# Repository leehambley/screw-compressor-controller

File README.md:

# Screw compressor controller

A replacement controller for a Ceccato ES3000-based 3-phase screw compressor
whose original control board died (blown triac, damaged optocouplers and
traces). It holds a pressure setpoint by running the motor's variable-frequency
drive at the right speed, watches the temperatures, and has a touch screen for
the operator.

*The operator screen (480×480). Rendered from the real UI source with the same
renderer and fonts the board uses; see [Previewing the UI](#previewing-the-ui).*

## The machine

| | |
|---|---|
| Compressor | Ceccato ES3000 screw compressor, rated 10 bar, run at 8 bar |
| Motor | WEG W22 Premium, 7.5 kW, 400 V, 2-pole, 50 Hz |
| Drive | SAKO SKI-70 VFD, controlled entirely over Modbus RTU (no analog speed signal) |
| Sensors | 2 × 4–20 mA pressure transmitters (0–17 bar), up to 3 × 100k NTC probes |
| Valves | start-assist (blow-down to intake) and condensate drain, both 24 V solenoids |

There is no load/unload air valve. Capacity is controlled by VFD speed alone:
a PID loop holds the setpoint pressure. The start-assist valve only works
during the start-up ramp, and the drain is manual or timed.

## Hardware

Two boards, stacked and screwed together, in one enclosure:

1. **Waveshare ESP32-S3-Touch-LCD-4, Rev 4.0**: the brain and the display.
   ESP32-S3-WROOM-1-N16R8 (16 MB flash, 8 MB PSRAM), 4″ 480×480 panel
   (ST7701S, RGB interface), GT911 capacitive touch, a CH32V003 helper chip
   (panel and touch resets, backlight), and an onboard RS485 transceiver.
2. **The [piggyback](Piggyback/)**: a 100 × 80 mm SMD board, assembled by
   JLCPCB, that does everything the Waveshare can't. It connects to the
   Waveshare through its 10-pin H4 header only (power, I²C and the RS485 pair),
   because every ESP32-S3 pin is already used by the display.

```mermaid
flowchart LR
    PSU["24 V DC supply"] --> PB
    subgraph Module["Display module (one stack)"]
        WS["Waveshare ESP32-S3-Touch-LCD-4<br/>touch UI, control loop"]
        PB["Piggyback I/O board"]
        WS <-->|"H4: 24 V, I²C, RS485"| PB
    end
    PB -->|"RS485 A/B (Modbus)"| VFD["SAKO SKI-70 VFD"]
    PB -->|"enable opto (X1)"| VFD
    P["2 × 4–20 mA pressure"] --> PB
    T["3 × NTC probes"] --> PB
    PB -->|"MOSFET + PWM hold"| V["start-assist and drain valves"]
```

### The piggyback

| Block | Parts |
|---|---|
| Analog inputs | 2 × ADS1115 (16-bit, I²C): two 4–20 mA loops through 100 Ω shunts, three NTC dividers |
| Valve drive | PCA9685 PWM chip, low-side MOSFETs, flyback diodes (full drive to pull in, then a PWM hold) |
| Over-temperature cutout | LM393 comparators on the rotor and motor NTCs, independent of the firmware |
| Watchdog | 74LVC1G123 monostable: the firmware must toggle a heartbeat line about 5 times a second |
| Safety gating | 74LVC08: valves and the VFD enable output only work while the watchdog **and** the temperature cutout are OK |
| VFD enable | optocoupler on the drive's X1 input, set to coast-stop when open |

If the S3 hangs, the piggyback loses power, or a probe reads too hot, the
valves drop out and the VFD's enable input opens, which is set up to coast the
motor to a stop, with no software involved (the drive setting is still to be
verified on the real drive). The
full design, pin allocation and mounting are in
[Piggyback/README.md](Piggyback/README.md) and
[Piggyback/pin-allocation.md](Piggyback/pin-allocation.md).

The piggyback screws to the back of the Waveshare on four 20 mm M2.5 standoffs:

```
 front ->  [ cover glass 84.2 x 84.2 ]
           [ Waveshare PCB 74.5 x 76.5 ]   H4 plug sticks out of its back face
                ||  4x M2.5 standoffs, 20 mm
           [ piggyback 100 x 80, parts facing away from the display ]
```

### Wiring

Only the pressure transmitter colours are fixed (brown = +24 V, green = signal). Every other colour marked "suggested" is a convention for this harness. Pick your own if you like, but use them consistently. The diagram is generated from the board's pad positions, so terminal order matches the silkscreen.

### VFD settings (SAKO SKI-70)

Set these on the drive's keypad before connecting the controller. Typically: PRG, arrows to the parameter, ENTER to edit, ENTER to store (check the manual for the exact keys).

| Parameter | Value | What it does |
|---|---|---|
| P0-02 | 2 | Run/stop commands come from comms (Modbus). |
| P0-03 | 9 | The speed setpoint comes from comms. |
| P0-12 | 35 Hz | Minimum frequency. The firmware reads it at start-up and keeps to the tighter of this and its own 35 Hz. |
| P0-14 | 50 Hz | Maximum frequency, also read at start-up. |
| Pd-00 | 5 | 9600 baud. |
| Pd-01 | 3 | 8N1 (8 data bits, no parity, 1 stop bit). |
| Pd-02 | 1 | Modbus address 1. |
| Accel / decel time | ≤ 5.5 s | The firmware assumes the motor is up to speed 5.5 s after a run command (`VFD_ACCEL_MS`). Parameter numbers are in the manual's P0 group. |
| Comms timeout | 2–3 s, stop or fault | If the manual's Pd group has one, set it. The controller talks to the drive every 0.5 s, so silence longer than this means the controller or the cable has failed. |

- **Recheck Pd-00..02 after a power cut.** They have been seen to reset. "VFD comms error" after an outage usually means this.
- Enter the motor nameplate data (and auto-tune, if offered) as the manual describes.

**Hardware stop on X1 (optional).** The piggyback can also stop the motor without the firmware: J10 (DI, COM) is an optocoupler that conducts only while SAFE is high. SAFE needs the watchdog heartbeat and the over-temperature comparator to be OK. Only set these if J10 DI is wired to X1 and COM to the drive's GND:

| Parameter | Value | What it does |
|---|---|---|
| P4-00 | 8 | X1 = coast to stop ("freely park"). Replaces the factory default 1 = FWD. |
| P4-35 | 00001 | X1 is active when low, so an open opto (SAFE low, controller dead, cable cut) coasts the motor. Modbus still controls run, stop and speed; X1 can only stop it. |

- **Without the X1 wire, leave both at their defaults.** P4-00 = 0 (no function) if the manual lists it, P4-35 = 00000. If you set them with X1 unwired, the open input means "stop" all the time and the motor never runs.
- When wired, test it: with the motor running over Modbus, unplug J10. The motor must coast to a stop.
- Don't use P4-00 = 32 ("outer failure normally close"). It latches Err15 at every power-up, before the heartbeat starts, and needs a manual reset each time.

## The screen

The UI is written in [Slint](https://slint.dev) and drawn by its software
renderer into a framebuffer in PSRAM. It shows the pressure large enough to read
from across the workshop, the setpoint with − and + buttons, motor speed and
estimated power, a status bar, and START / STOP / RESET plus hold-to-act UNLOAD
and PURGE buttons. Setpoint changes are saved to flash.

| Standby, minimum speed | Fault |
|---|---|
|  |  |

## Firmware

[Software/](Software/) is a `no_std` Rust program for the ESP32-S3:
[esp-hal](https://github.com/esp-rs/esp-hal) 1.0 with Embassy running on
`esp-rtos`.

| Module | What it does |
|---|---|
| `main.rs` | start-up, then one loop: read sensors, run the state machine, update the UI |
| `state_machine.rs` | Idle, Unloading (open-loop fill), Running (PID), UnloadIdle, Stopping, Fault; start-rate limit; over-pressure and over-temperature cutouts |
| `pid.rs`, `modbus.rs` | speed loop; Modbus RTU to the SKI-70 |
| `sensors.rs`, `valve.rs`, `outputs.rs` | 4–20 mA and NTC conversion; valve pull-in and PWM hold; heartbeat and status LEDs |
| `storage.rs` | start count, runtime and setpoint, kept in flash across power cycles |
| `ui.rs`, `ui/main.slint` | the screen and touch input |
| `board/` | drivers for the Waveshare board (panel, touch, expander) and the piggyback chips |

The control constants (pressure thresholds, temperature limits, VFD speed
limits, PID gains) are in `src/config.rs`. [Software/CLAUDE.md](Software/CLAUDE.md)
holds the long-form notes: what was measured, what was decided and why.

### Building and flashing

You need Espressif's Xtensa Rust toolchain (the S3 isn't supported by stock Rust):

```sh
cargo install espup espflash
espup install --targets esp32s3
. ~/export-esp.sh
```

Then, from `Software/`, with the board plugged into its USB-C port:

```sh
cargo run --release
```

This flashes over the board's USB-Serial-JTAG and shows the log. There is
also a `vfd-run-test` binary for exercising the drive on its own.

### How the display works

Driving a 480×480 RGB panel from PSRAM with a Rust HAL needed a few things
the HAL doesn't do for you. They are written up in the source:
[Software/src/board/display.rs](Software/src/board/display.rs) (scan-out from
SRAM bounce buffers, start order, vsync re-sync) and
[Software/src/board/st7701/](Software/src/board/st7701/) (the panel's init
sequence, with named registers).

## Status

- **Working on the bench:** display, touch, the UI, and saving the setpoint.
- **Next:** wiring up and testing the piggyback (sensors, valves, watchdog),
  then Modbus to the VFD on the new hardware.
- **Not done:** bold text in the UI (needs a variable font), and the control
  loop has not yet run against a real compressor on this hardware.

## Repository layout

| Path | Contents |
|---|---|
| [`Software/`](Software/) | the firmware (Rust) |
| [`Piggyback/`](Piggyback/) | the piggyback board: KiCad project, JLCPCB production files, notes |
| [`Main/`](Main/) | the original controller board, for the retired ESP32-C6 and Nextion design |
| [`THT/`](THT/) | a through-hole version of the breadboard controller, for hand soldering |
| [`docs/`](docs/) | images used in this README |
| [`tools/`](tools/) | `ui-preview`, which renders the UI to PNG |

The project started on an ESP32-C6 with a Nextion display. It moved to the
Waveshare S3 board in November 2026; the earlier design remains in the git
history.

## Previewing the UI

The screenshots above are not photographs. They are rendered on a computer from
`Software/ui/main.slint` with the same software renderer, fonts and RGB565 colour
depth as the board. To regenerate them after changing the UI:

```sh
cd tools/ui-preview
cargo run --release -- ../../docs/images
```

The scenes (running, standby, fault) are defined at the top of
`tools/ui-preview/src/main.rs`.

## Checks

The panel's init sequence is held to a golden test that needs no hardware:

```sh
cd Software/tools
rustc --edition 2024 -o /tmp/st7701_golden st7701_golden.rs && /tmp/st7701_golden
```

The beeper timing (docs/alerts.md) has one too:

```sh
cd Software/tools
rustc --edition 2024 -o /tmp/alarm_check alarm_check.rs && /tmp/alarm_check
```

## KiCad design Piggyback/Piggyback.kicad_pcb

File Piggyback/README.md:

# Piggyback I/O board for the Waveshare ESP32-S3-Touch-LCD-4

An SMD board, assembled by JLCPCB, that carries everything the Waveshare
display board can't do itself. It connects to the board's 10-pin H4 header
only: power, I2C and the RS485 pair. Every S3 GPIO is taken (see
[pin-allocation.md](pin-allocation.md)).

**2026-11-04 evening: the display board changed from the 5" to the 4" (480x480).**
The changes that followed:
- J2 is now a 10-pin H4 harness.
- The heartbeat comes from PCA9685 LED4, not the Waveshare's DO0.
- The status lines back to the S3 (Q5/Q6) are gone. The S3 reads SAFE and TEMP_OK through the ADS1115s.
- New J11 passes Modbus A/B through to the VFD.

Lee confirmed the onboard RS485 transceiver (no isolation) and no digital inputs.

**Rev 4.0 (current production, checked 2026-11-04):**
- The transceiver is an SP3485 with RC auto-direction. It is not a MAX13487.
- UART0 is TX GPIO44 / RX GPIO43.
- The expander is a CH32V003 at 0x24.
- H4 is a **3.5 mm 10-pin pluggable screw terminal**, so J2 must mate with that.

Details are in [pin-allocation.md](pin-allocation.md).
The blocks below still describe the original 8-pin J2. The schematic is authoritative.

## Decisions (Lee, 2026-11-04)

- The S3 is the only MCU and runs all-Rust Embassy (Xtensa). The C6 and the Nextion are retired.
- Modbus to the SKI-70 goes through the Waveshare's onboard RS485 transceiver (UART0, TX 44 / RX 43, auto direction, not isolated).
  The piggyback has no RS485 parts.
- The valves are driven by MOSFETs on the piggyback, with the PWM hold kept.
- Fail-safe: a firmware watchdog **and** a hardware over-temperature cutout.
- NTC pull-up is 33k. The pressure shunt is 100 Ω, 0–17 bar, as in `Software/src/config.rs`.
- No TPS5430 and no NMA0505/ADM2483. The Waveshare runs from 24 V on its own VIN.

## Blocks

### Power
- J1: 24 V in, 2-pin pluggable terminal, 5.08 mm.
- Protection chain: polyfuse (≥ 30 V rated, ~1.5 A hold), then a series Schottky SS54 for reverse polarity, then an SMBJ30A TVS.
  The result is **24V_P**.
- 24V_P feeds the Waveshare VIN (via J2), both valves and both 4–20 mA loops.
- 3V3 comes from the Waveshare's own 3V3 rail: P1 pin 3 "I2C_VCC", with jumper H8 set to 3V3.
  The piggyback load is about 30 mA.
  - **3V3_D** = logic.
  - **3V3_A** = 3V3_D through a 600 Ω ferrite bead plus 10 µF and 100 nF. It feeds the ADS1115s, the NTC dividers and the comparator references.
- If the Waveshare 3V3 dies, all piggyback outputs drop. That is fail-safe by construction.

### J2: harness to Waveshare P1 (8-pin pluggable, 3.5 mm)

| J2 | Net | Waveshare P1 |
|---|---|---|
| 1 | 24V_P | 1 VIN |
| 2 | GND | 2 GND |
| 3 | 3V3_D | 3 I2C_VCC |
| 4 | SDA | 5 D_SDA |
| 5 | SCL | 6 D_SCL |
| 6 | HEARTBEAT | 11 DOUT0 |
| 7 | DIN_TEMP | 15 DIN0 |
| 8 | DIN_WD | 16 DIN1 |

- The Waveshare already pulls SDA and SCL up with 4.7k. The piggyback has DNP 4.7k footprints only.
- J5 is a 4-pin 3.5 mm screw-flange pluggable terminal for I2C expansion (3V3_D, GND, SDA, SCL), LCSC C5188343. It is DNP: not in the JLC BOM/CPL, hand-fit. The mating plug is 15EDGKM-3.5-04P.

### Analog inputs: 2× ADS1115 (16-bit, I2C)

U1 is at 0x48 (ADDR = GND):
- AIN0 = pressure 1, AIN1 = pressure 2.
- AIN2 = 3V3_A / 2, through a 10k/10k divider, so the NTC math can be ratiometric.
- AIN3 = SAFE / 2, through a 10k/10k divider.

U2 is at 0x49 (ADDR = VDD):
- AIN0 = NTC1 (rotor, primary), AIN1 = NTC2 (rotor, secondary), AIN2 = NTC3 (motor).
- AIN3 is spare and goes to a test point.

Both run from 3V3_A, and ALERT/RDY are not connected.

**4–20 mA (×2):**
- Terminal: 2-pin 5.08, LOOP+ and SIG.
- LOOP+ = 24V_P through a 50 mA PTC per channel.
- SIG goes to GND through a 100 Ω 1 % 1206 shunt (JLC Basic part; calibrate the gain in firmware).
- The shunt node goes through 1k to the ADC pin. At the pin: 100 nF to GND and a BAV99 clamp to 3V3_A / GND.
- 20 mA gives 2.0 V. Firmware sets the PGA to ±4.096 V and flags readings below 3.8 mA as open loop.

**NTC (×3), 100k B≈4000:**
- Terminal: 3-pin 5.08, NTC, AGND, SHIELD (shield goes to AGND at this end only).
- 3V3_A → 33k 1 % → NTCn_NODE (1 % costs about 0.35 K at 100 °C), which goes to the terminal; the probe returns to AGND.
- NTCn_NODE → 10k → ADC pin, with 100 nF to AGND and a BAV99 clamp. The 10k limits fault current into the ADS1115 well below its 10 mA input rating.
- ESD diode footprint (PESD5V0S1BA, D5–D7) at each terminal pin, DNP to save a JLC Extended part. The 33k/10k/100k resistors and the 100 nF take most of an ESD hit; hand-fit the diodes if the sensor cables prove troublesome.

### Hardware over-temperature cutout: LM393 dual comparator on 3V3_A

The comparators take NTC1 and NTC3 as inputs. The thresholds are ratiometric dividers from 3V3_A.

| Ch | Input | Trip | Threshold divider (IN−) | Node at trip |
|---|---|---|---|---|
| A | NTC1 rotor | ≈ 111 °C (firmware trips at 105) | 100k / 15k (0.1304·Vcc) | 0.43 V |
| B | NTC3 motor | ≈ 138.5 °C (firmware faults at 130) | 100k / 7.5k (0.0698·Vcc) | 0.23 V |

- IN+ = NTCn_NODE through 100k. Hysteresis comes from 10 MΩ output→IN+ (about 3 K). The load this puts on the NTC node is below 0.2 K.
- The open-collector outputs are wire-ANDed with a 10k pull-up to 3V3_D. That gives **TEMP_OK**: high = OK, low = too hot.
- An open probe reads cold, so firmware catches it on the ADS (voltage-window check).

### Firmware watchdog: 74LVC1G123 retriggerable monostable

- HEARTBEAT is DOUT0, the Waveshare's NPN open collector to GND. It is pulled up to 3V3_D with 10k and feeds the B input. A is tied low and CLR high.
- Rx/Cx set tw to about 1 s. Firmware toggles DOUT0 at about 5 Hz.
- Q = **WD_OK**. It is low at power-up, and goes low again if the heartbeat stops in either state.

### Safety gating: 74LVC08 quad AND (3V3_D)

- Gate A: SAFE = WD_OK · TEMP_OK
- Gate B: V1_DRV = PCA_LED0 · SAFE
- Gate C: V2_DRV = PCA_LED1 · SAFE
- Gate D: VFD_EN = SAFE · SAFE, which drives the VFD enable opto.

**Status back to the S3:**
- Two 2N7002s pull DIN0 / DIN1 low when TEMP_OK / WD_OK are high.
- The Waveshare biases its DIN inputs from its own 5 V through 3.6k plus the opto LED.

### Valve PWM: PCA9685 (0x40, A0–A5 = GND, OE = GND, EXTCLK = GND)

- LED0 = start-assist valve, LED1 = drain valve.
- LED2 and LED3 drive status LEDs. LED4–15 are not connected.
- Firmware runs it at about 1.5 kHz (maximum prescale rate) with a 50 % hold after the pull-in time.

### Valve drivers (×2)

- Vn_DRV → 100 Ω → gate of an N-MOSFET, with 100k gate to GND.
- The MOSFET is logic-level: ≥ 60 V, ≥ 2 A, R_DS(on) < 100 mΩ at 2.5–3.3 V, SOT-23 or SOT-23-3 class. It is low-side.
- Flyback: SS34 Schottky across the coil (cathode to 24V_P).
- Indicator: LED + 10k from 24V_P to the drain.
- Terminal: 4-pin 5.08 (V1+, V1−, V2+, V2−). The + pins are 24V_P.
- Loads: start-assist about 290 mA, drain about 375 mA.

### VFD enable output

- VFD_EN → 330 Ω → LED of a PC817-class optocoupler (LTV-817S, SMD).
- The transistor goes to J10, a 2-pin 5.08 terminal (DI, COM). Wire DI to SKI-70 **X1** and COM to the
  drive's **GND** (COM on the isolated variant). The drive's inputs are switched to GND (5–30 V, 1 kΩ).
- SKI-70 settings (manual, P4 group), alongside the Modbus ones (P0-02=2, P0-03=9, Pd-00..02):
  - **P4-00 = 8** ("freely park", i.e. coast to stop). The factory default 1 = FWD must go.
  - **P4-35 = 00001**: X1 active on *low* level, so an **open** opto (SAFE low, piggyback or S3 dead,
    cable cut) coasts the motor. Terminal functions act independently of the command source, so
    Modbus keeps run/stop/speed while X1 can only stop it. **Verify on the drive**: with the motor
    running over Modbus, pulling J10 must coast it to a stop; the manual's table doesn't say so explicitly.
  - Coast-stop doesn't latch, so no fault reset is needed. The alternative, P4-00 = 32
    ("outer failure normally close"), trips Err15. That latches, and it would also trip at every
    power-up before the heartbeat starts, so it would need a reset (keypad or X4 = 9) each time.
    The manual doesn't document a Modbus fault-reset command.
- The opto conducts only while SAFE is high. So a dead piggyback, a dead S3 or an over-temperature condition stops the motor.

## Mechanical: screwed to the back of the Waveshare (Lee approved 2026-11-04)

```
 front ->  [ cover glass 84.2 x 84.2 ]
           [ Waveshare PCB 74.5 x 76.5 ]   H4 plug sticks out of its back face
                ||  4x M2.5 standoffs, 20 mm (F-F), on the 66.50 x 68.50 mm pattern
           [ piggyback 100 x 80, parts facing away from the display ]
                ||  optional standoffs / DIN carrier to the enclosure
```

- The piggyback repeats the Waveshare's hole pattern (66.50 × 68.50 mm) centred on its own outline.
  Screws go through the piggyback into the standoffs, and through the standoffs into the Waveshare.
  The display and the piggyback become one rigid module.
- Hole size: **2.7 mm (M2.5) assumed**. The Waveshare drawing gives no diameter.
  Measure the board when it arrives; the piggyback can take 3.2 mm (M3) if the Waveshare holes are M3.
- The standoffs are 20 mm. That clears the green H4 plug (wires enter it sideways, towards the Waveshare's bottom edge), the battery header and the buzzer.
- Harness: a short 10-wire loom. The Waveshare's own H4 plug sits at one end, and a 10P plug mates J2 at the other. J2 is **3.50 mm pitch** (pin 1 to pin 10 = 31.5 mm), THT right-angle header, 1.2 mm holes (LCSC C5188303 / Phoenix MC 1,5/10-G-3,5; plug MC 1,5/10-ST-3,5). "15EDG" listings come in both 3.5 and 3.81 mm: 3.81 does not fit.
  Use 0.5 mm² for VIN/GND and a twisted pair for A/B.
- **Keep-outs on the piggyback's display-facing side**: no tall parts under the H4 plug footprint.
  That is the Waveshare's lower edge, 41 mm wide, centred 11.08 + 20.5 mm from its left edge.
  All piggyback parts go on the far side anyway.
- Field terminals sit on all four edges, outside the Waveshare footprint:
  - Left: J2 (harness to H4), J11 Modbus.
  - Bottom: J1 24 V, J9 valves, J10 VFD enable.
  - Top: J6–J8 NTC.
  - Right: J3/J4 4–20 mA, J5 I2C expansion.

## Layout intent

- 100 × 80 mm, 2 layers. 4× M2.5 holes on the Waveshare pattern (see Mechanical).
- Valve drivers, 24 V entry and TVS on one side; ADS, NTC and 4–20 mA front end on the other.
- Routed with Freerouting (all nets, GND and AGND included) and then poured: GND on both layers, AGND (priority 1, solid pad connection) over the analog block. AGND and GND tie at one point through R1.
- Netclasses: Default 0.3 mm / 0.15 mm clearance; Power24 (24V_IN, FUSE_OUT, 24V_P) 0.8 mm with 1.1/0.5 vias; Rail (VALVE1-, VALVE2-) 0.5 mm with 0.8/0.4 vias.
- 100 × 80 mm with 2 mm corner radius. DRC: 0 errors, 0 unconnected.

## Production

`./production/make_production.sh` (run from `Piggyback/`) regenerates the gerbers and drill zip, the JLC BOM and CPL, and the renders. Parts are chosen from JLC's Basic library wherever one fits, because each Extended part adds a feeder-loading fee. DNP parts (Value or `Assembly` field containing "DNP": R2, R3 and all J connectors, which are hand-fit) and parts without an LCSC number are left out of the BOM and CPL.

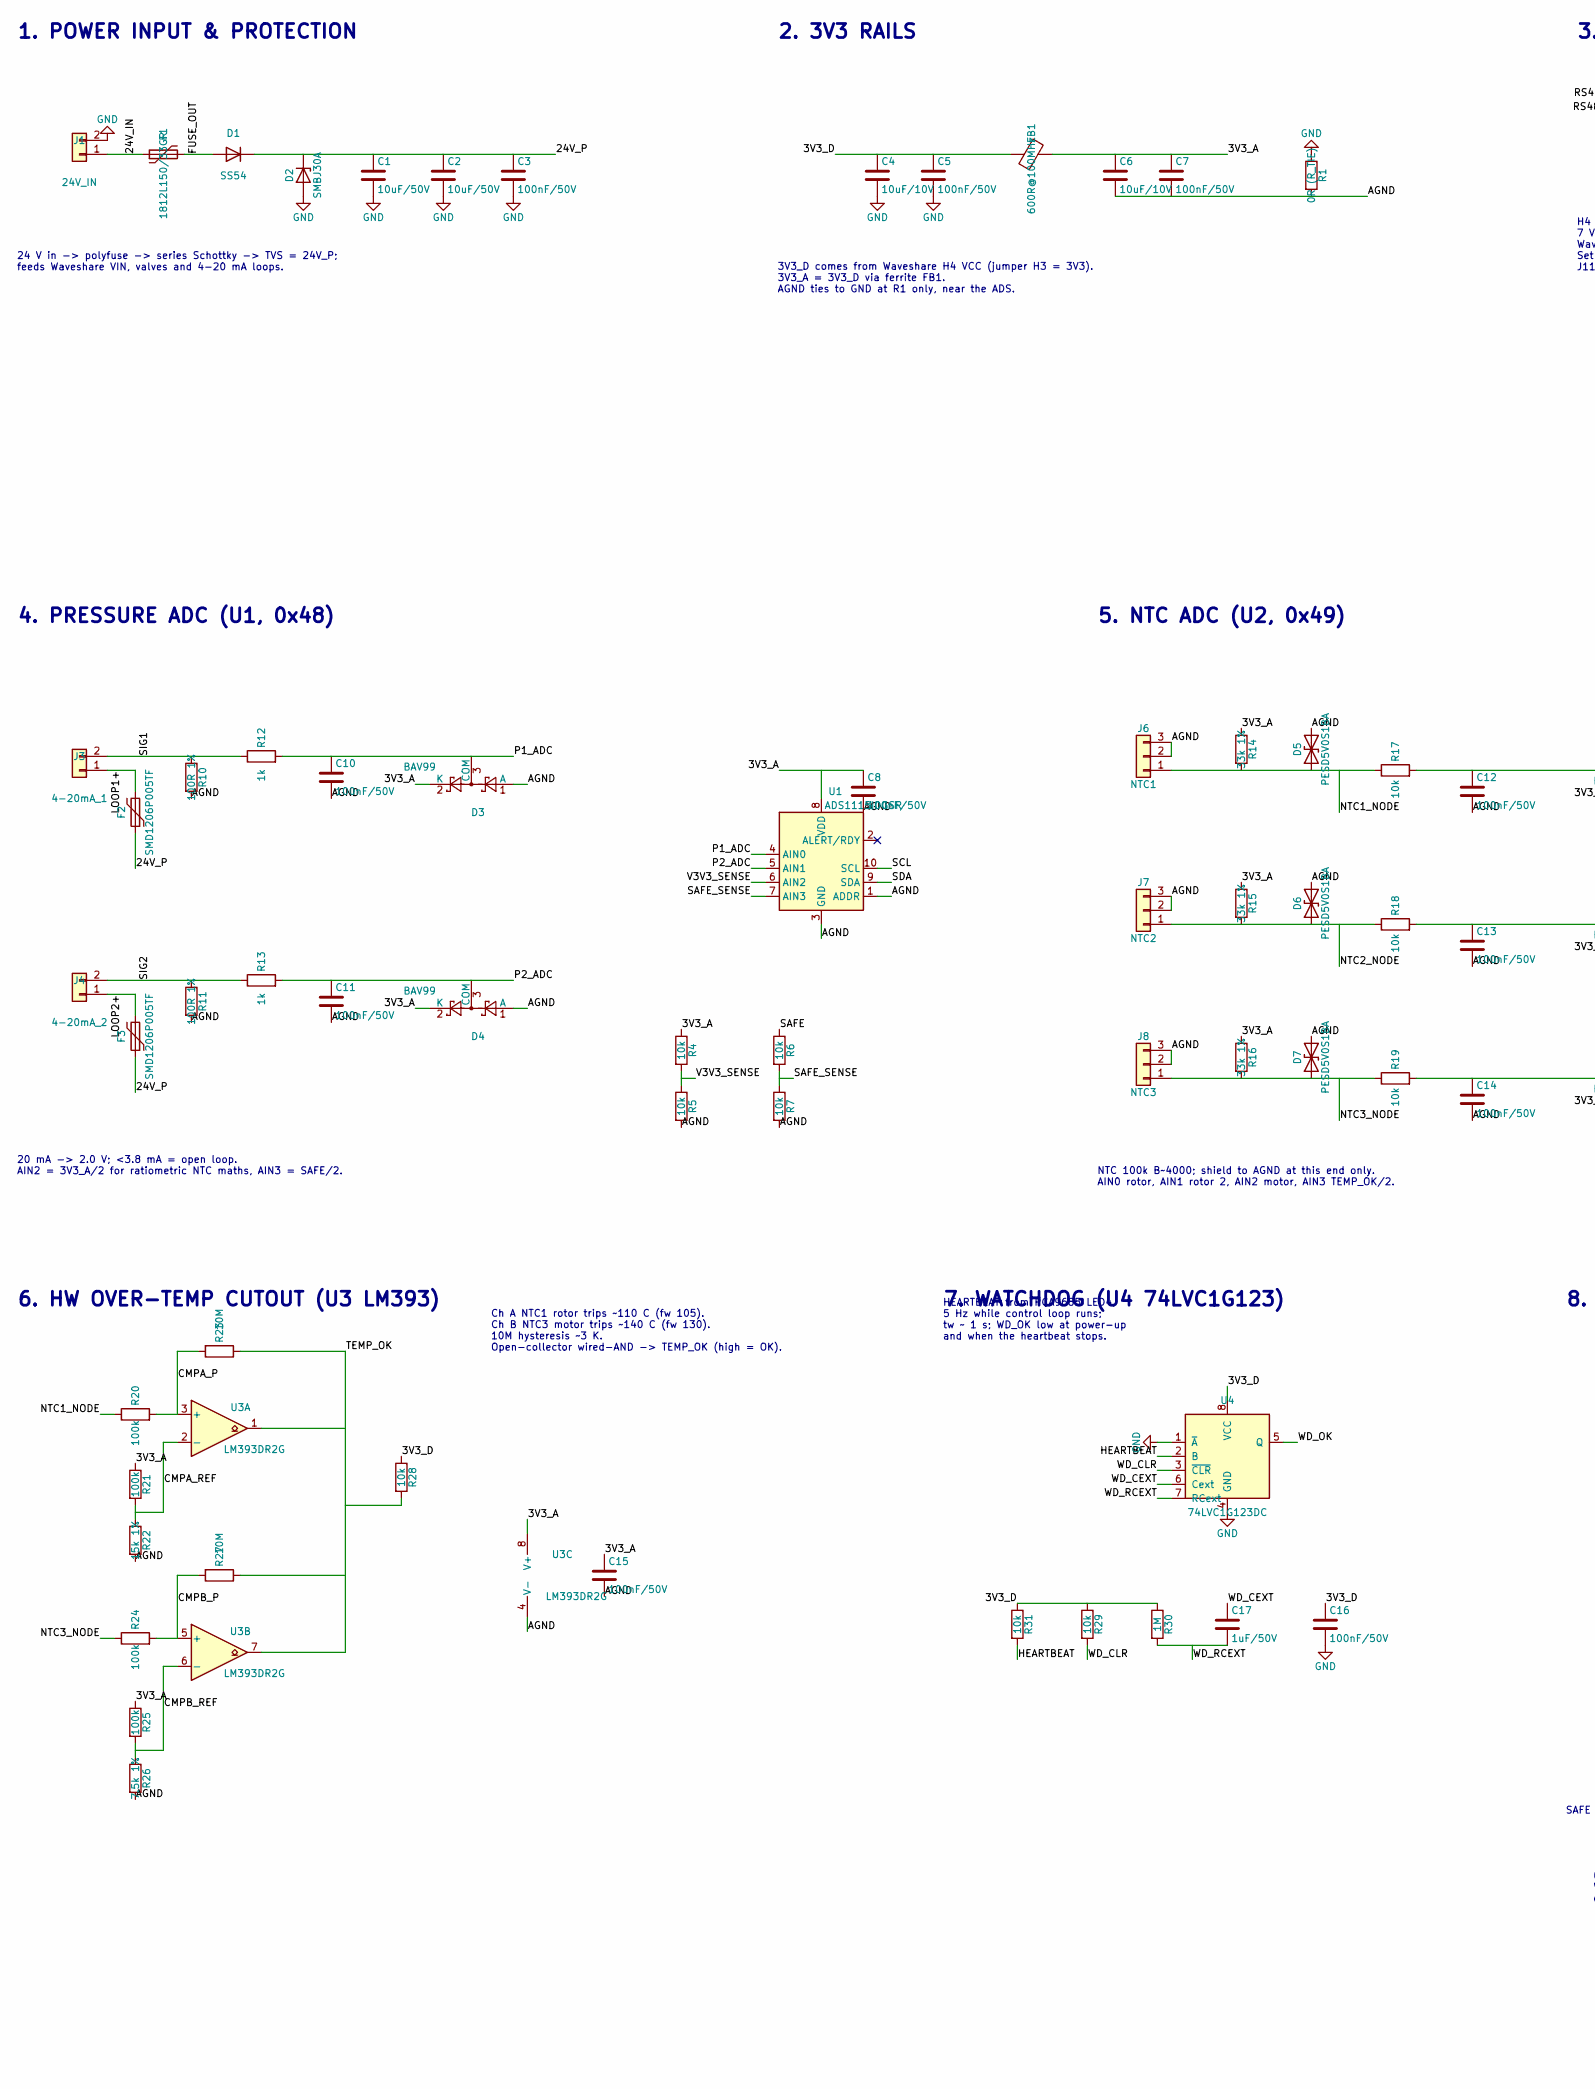
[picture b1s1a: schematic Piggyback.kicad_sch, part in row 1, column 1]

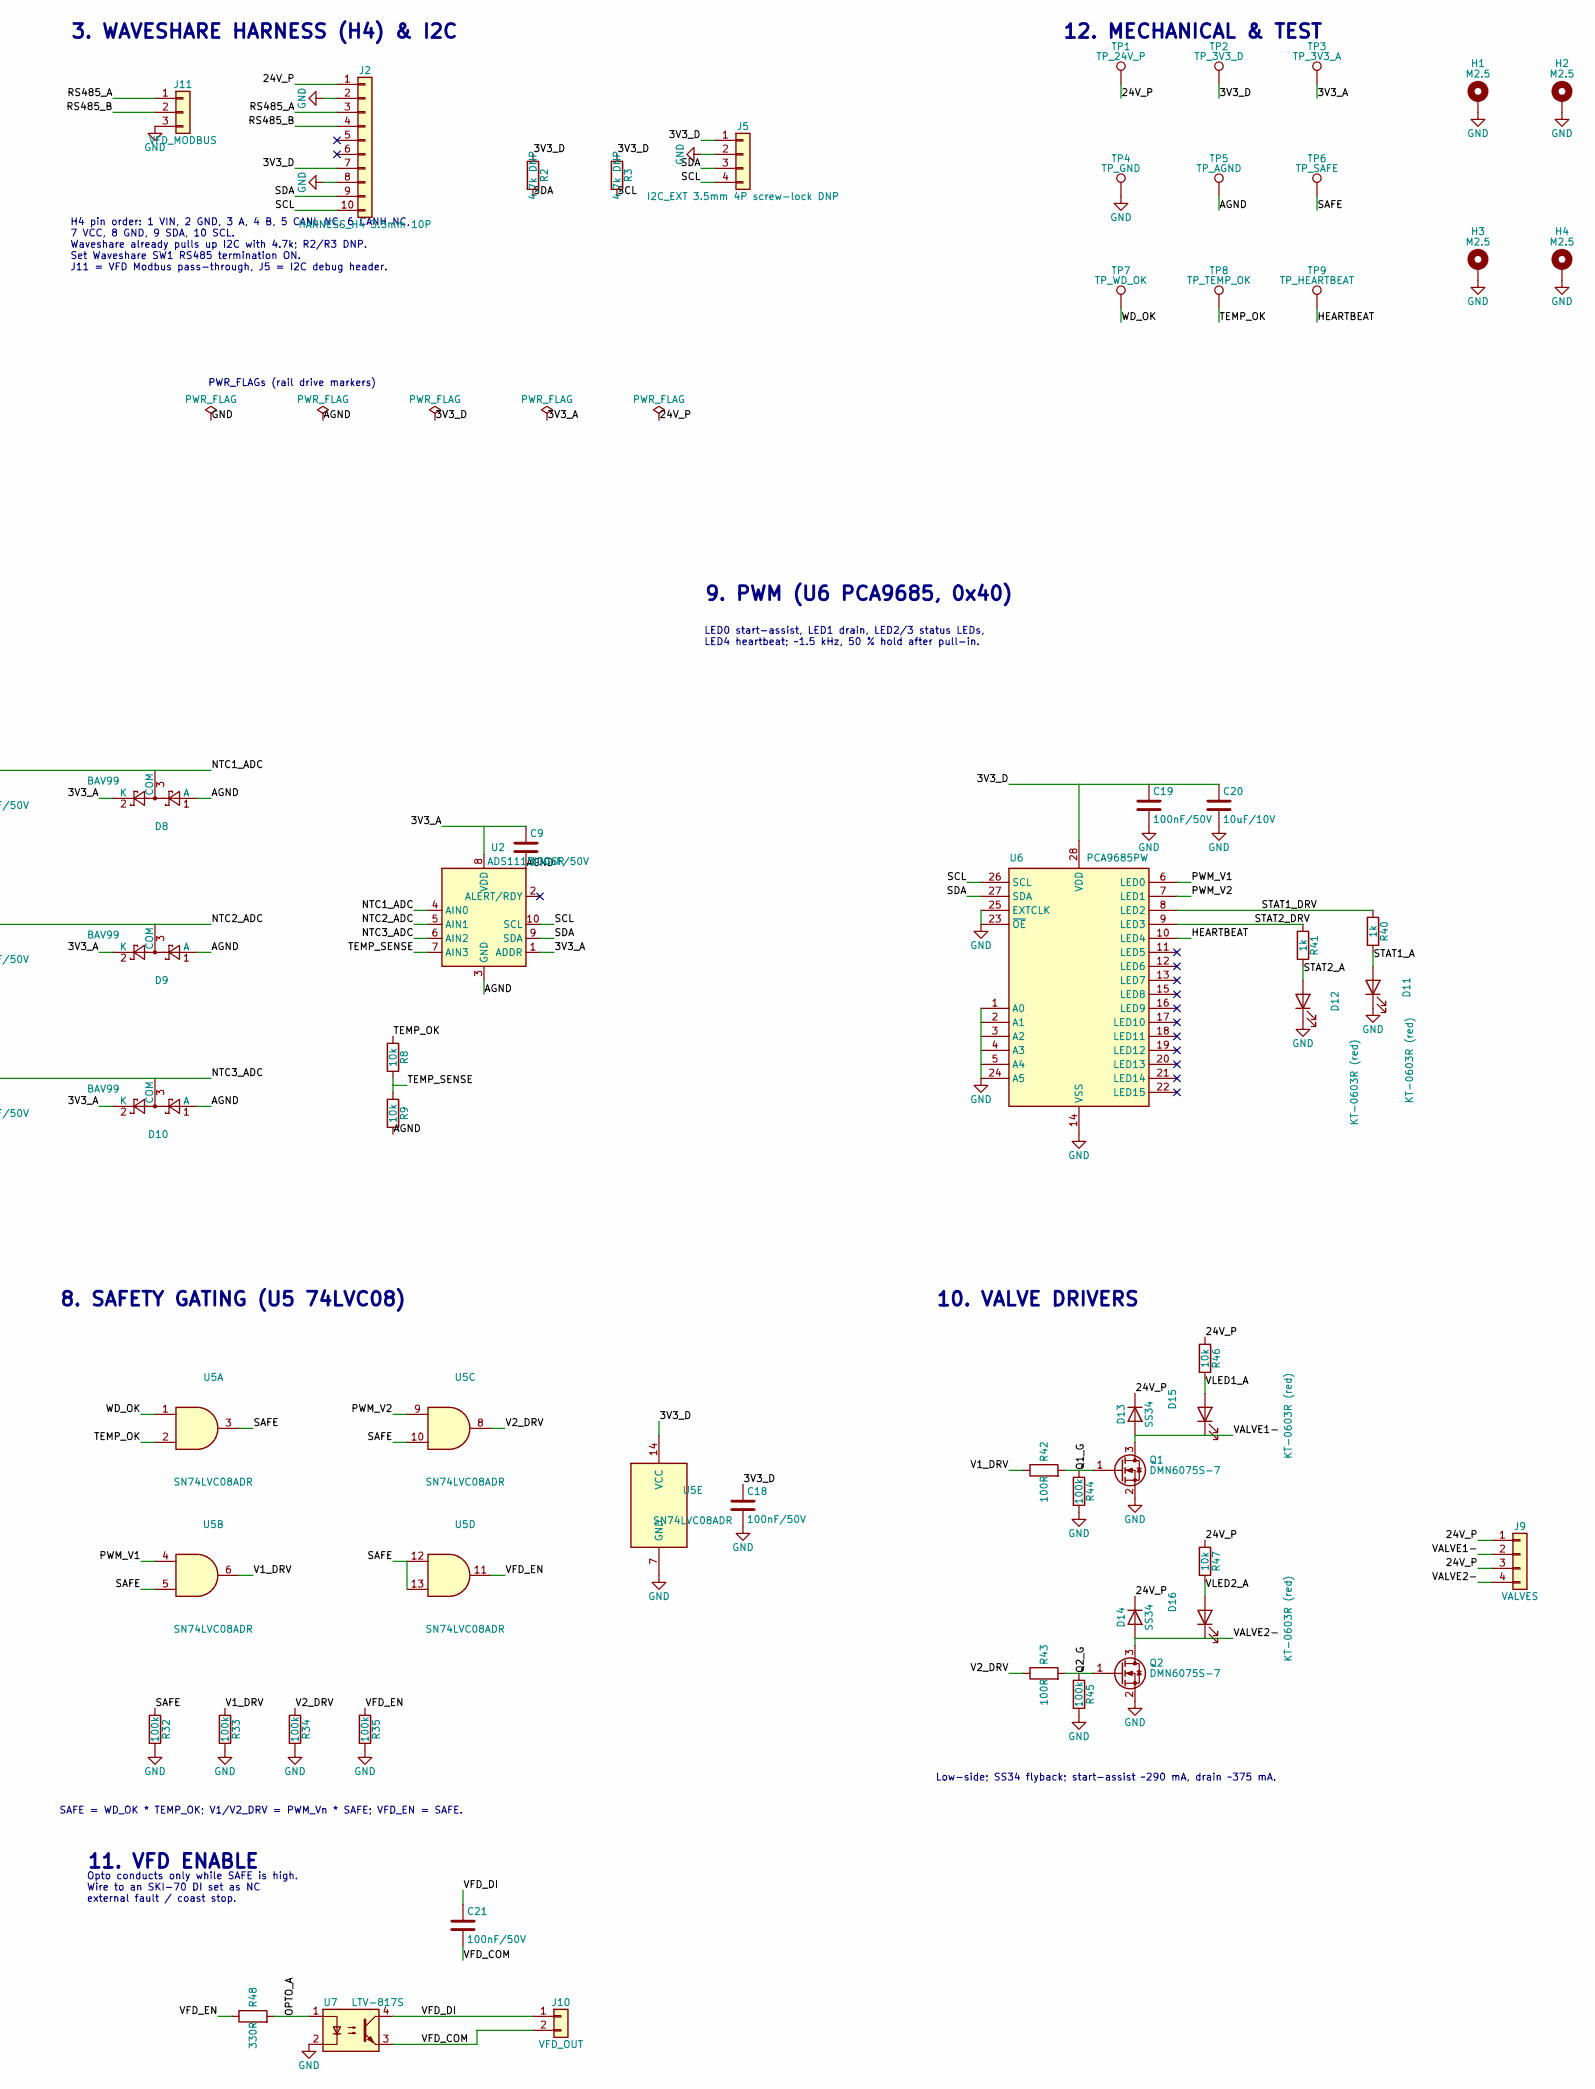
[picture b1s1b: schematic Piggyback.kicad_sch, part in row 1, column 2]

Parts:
C1, C2: 10uF/50V; C_1206_3216Metric; MPN CL31A106KBHNNNE; LCSC C13585
C3, C5, C7, C8, C9, C10, C11, C12, C13, C14, C15, C16, C18, C19, C21: 100nF/50V; C_0603_1608Metric; MPN CC0603KRX7R9BB104; LCSC C14663
C4, C6, C20: 10uF/10V; C_0603_1608Metric; MPN CL10A106KP8NNNC; LCSC C19702
C17: 1uF/50V; C_0603_1608Metric; MPN CL10A105KB8NNNC; LCSC C15849
D1: SS54; D_SMA; MPN SS54; LCSC C22452
D2: SMBJ30A; D_SMB; MPN SMBJ30A; LCSC C113998
D3, D4, D8, D9, D10: BAV99; SOT-23; MPN BAV99,215; LCSC C2500
D5, D6, D7: PESD5V0S1BA; D_SOD-323; MPN PESD5V0S1BA,115; LCSC C19224
D11, D12, D15, D16: KT-0603R (red); LED_0603_1608Metric; MPN KT-0603R; LCSC C2286
D13, D14: SS34; D_SMA; MPN SS34; LCSC C8678
F1: 1812L150/33GR; Fuse_1812_4532Metric; MPN 1812L150/33GR; LCSC C18198333
F2, F3: SMD1206P005TF; Fuse_1206_3216Metric; MPN SMD1206P005TF; LCSC C20797
FB1: 600R@100MHz; L_0603_1608Metric; MPN GZ1608D601TF; LCSC C1002
H1, H2, H3, H4: M2.5; MountingHole_2.7mm_M2.5_Pad
J1: 24V_IN; PhoenixContact_MSTBA_2,5_2-G-5,08_1x02_P5.08mm_Horizontal; MPN KF2EDGR-5.08-2P; LCSC C441204
J2: HARNESS_H4 3.5mm 10P; PhoenixContact_MC_1,5_10-G-3.5_1x10_P3.50mm_Horizontal; MPN MX15EDGRC-3.5-10P-GN01-Cu-A; LCSC C5188303
J3: 4-20mA_1; PhoenixContact_MSTBA_2,5_2-G-5,08_1x02_P5.08mm_Horizontal; MPN KF2EDGR-5.08-2P; LCSC C441204
J4: 4-20mA_2; PhoenixContact_MSTBA_2,5_2-G-5,08_1x02_P5.08mm_Horizontal; MPN KF2EDGR-5.08-2P; LCSC C441204
J5: I2C_EXT 3.5mm 4P screw-lock DNP; PhoenixContact_MC_1,5_4-GF-3.5_1x04_P3.50mm_Horizontal_Thre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; MPN MX15EDGRM-3.5-04P-GN01-Cu-A; LCSC C5188343
J6: NTC1; PhoenixContact_MSTBA_2,5_3-G-5,08_1x03_P5.08mm_Horizontal; MPN KF2EDGR-5.08-3P; LCSC C441205
J7: NTC2; PhoenixContact_MSTBA_2,5_3-G-5,08_1x03_P5.08mm_Horizontal; MPN KF2EDGR-5.08-3P; LCSC C441205
J8: NTC3; PhoenixContact_MSTBA_2,5_3-G-5,08_1x03_P5.08mm_Horizontal; MPN KF2EDGR-5.08-3P; LCSC C441205
J9: VALVES; PhoenixContact_MSTBA_2,5_4-G-5,08_1x04_P5.08mm_Horizontal; MPN KF2EDGR-5.08-4P; LCSC C441206
J10: VFD_OUT; PhoenixContact_MSTBA_2,5_2-G-5,08_1x02_P5.08mm_Horizontal; MPN KF2EDGR-5.08-2P; LCSC C441204
J11: VFD_MODBUS; PhoenixContact_MSTBA_2,5_3-G-5,08_1x03_P5.08mm_Horizontal; MPN KF2EDGR-5.08-3P; LCSC C441205
Q1, Q2: DMN6075S-7; SOT-23; MPN DMN6075S-7; LCSC C155242
R1: 0R (R_TIE); R_0603_1608Metric; MPN 0603WAF0000T5E; LCSC C21189
R2, R3: 4.7k DNP; R_0603_1608Metric; MPN 0603WAF4701T5E; LCSC C23162
R4, R5, R6, R7, R8, R9, R17, R18, R19, R28, R29, R31, R46, R47: 10k; R_0603_1608Metric; MPN 0603WAF1002T5E; LCSC C25804
R10, R11: 100R 1%; R_1206_3216Metric; MPN 1206W4F1000T5E; LCSC C17901
R12, R13, R40, R41: 1k; R_0603_1608Metric; MPN 0603WAF1001T5E; LCSC C21190
R14, R15, R16: 33k 1%; R_0603_1608Metric; MPN 0603WAF3302T5E; LCSC C4216
R20, R21, R24, R25, R32, R33, R34, R35, R44, R45: 100k; R_0603_1608Metric; MPN 0603WAF1003T5E; LCSC C25803
R22: 15k 1%; R_0603_1608Metric; MPN 0603WAF1502T5E; LCSC C22809
R23, R27: 10M; R_0603_1608Metric; MPN 0603WAF1005T5E; LCSC C7250
R26: 7.5k 1%; R_0603_1608Metric; MPN 0603WAF7501T5E; LCSC C23234
R30: 1M; R_0603_1608Metric; MPN 0603WAF1004T5E; LCSC C22935
R42, R43: 100R; R_0603_1608Metric; MPN 0603WAF1000T5E; LCSC C22775
R48: 330R; R_0603_1608Metric; MPN 0603WAF3300T5E; LCSC C23138
TP1: TP_24V_P; TestPoint_Pad_D1.0mm
TP2: TP_3V3_D; TestPoint_Pad_D1.0mm
TP3: TP_3V3_A; TestPoint_Pad_D1.0mm
TP4: TP_GND; TestPoint_Pad_D1.0mm
TP5: TP_AGND; TestPoint_Pad_D1.0mm
TP6: TP_SAFE; TestPoint_Pad_D1.0mm
TP7: TP_WD_OK; TestPoint_Pad_D1.0mm
TP8: TP_TEMP_OK; TestPoint_Pad_D1.0mm
TP9: TP_HEARTBEAT; TestPoint_Pad_D1.0mm
U1, U2: ADS1115IDGSR; TSSOP-10_3x3mm_P0.5mm; MPN ADS1115IDGSR; LCSC C37593
U3: LM393DR2G; SOIC-8_3.9x4.9mm_P1.27mm; MPN LM393DR2G; LCSC C7955
U4: 74LVC1G123DC; VSSOP-8_2.3x2mm_P0.5mm; MPN 74LVC1G123DC,125; LCSC C77273
U5: SN74LVC08ADR; SOIC-14_3.9x8.7mm_P1.27mm; MPN SN74LVC08ADR; LCSC C468253
U6: PCA9685PW; TSSOP-28_4.4x9.7mm_P0.65mm; MPN PCA9685PW,118; LCSC C2678753
U7: LTV-817S; SMDIP-4_W9.53mm; MPN LTV-817S-TA1-C; LCSC C109227

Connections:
/24V_IN: F1.1, J1.1
/CMPA_P: R20.2, R23.2, U3.3 (+)
/CMPA_REF: R21.2, R22.1, U3.2 (-)
/CMPB_P: R24.2, R27.2, U3.5 (+)
/CMPB_REF: R25.2, R26.1, U3.6 (-)
/FUSE_OUT: D1.2 (A), F1.2
/HEARTBEAT: R31.2, TP9.1 (1_1), U4.2 (B), U6.10 (LED4)
/LOOP1+: F2.2, J3.1
/LOOP2+: F3.2, J4.1
/NTC1_ADC: C12.1, D8.3 (COM), R17.2, U2.4 (AIN0)
/NTC1_NODE: D5.1 (A1), J6.1, R14.2, R17.1, R20.1
/NTC2_ADC: C13.1, D9.3 (COM), R18.2, U2.5 (AIN1)
/NTC2_NODE: D6.1 (A1), J7.1, R15.2, R18.1
/NTC3_ADC: C14.1, D10.3 (COM), R19.2, U2.6 (AIN2)
/NTC3_NODE: D7.1 (A1), J8.1, R16.2, R19.1, R24.1
/OPTO_A: R48.2, U7.1
/P1_ADC: C10.1, D3.3 (COM), R12.2, U1.4 (AIN0)
/P2_ADC: C11.1, D4.3 (COM), R13.2, U1.5 (AIN1)
/PWM_V1: U5.4, U6.6 (LED0)
/PWM_V2: U5.9, U6.7 (LED1)
/Q1_G: Q1.1 (G), R42.2, R44.1
/Q2_G: Q2.1 (G), R43.2, R45.1
/RS485_A: J2.3, J11.1
/RS485_B: J2.4, J11.2
/SAFE: R6.1, R32.1, TP6.1 (1_1), U5.3, U5.5, U5.10, U5.12, U5.13
/SAFE_SENSE: R6.2, R7.1, U1.7 (AIN3)
/SCL: J2.10, J5.4, R3.2, U1.10 (SCL), U2.10 (SCL), U6.26 (SCL)
/SDA: J2.9, J5.3, R2.2, U1.9 (SDA), U2.9 (SDA), U6.27 (SDA)
/SIG1: J3.2, R10.1, R12.1
/SIG2: J4.2, R11.1, R13.1
/STAT1_A: D11.2 (A), R40.2
/STAT1_DRV: R40.1, U6.8 (LED2)
/STAT2_A: D12.2 (A), R41.2
/STAT2_DRV: R41.1, U6.9 (LED3)
/TEMP_OK: R8.1, R23.1, R27.1, R28.2, TP8.1 (1_1), U3.1, U3.7, U5.2
/TEMP_SENSE: R8.2, R9.1, U2.7 (AIN3)
/V1_DRV: R33.1, R42.1, U5.6
/V2_DRV: R34.1, R43.1, U5.8
/V3V3_SENSE: R4.2, R5.1, U1.6 (AIN2)
/VALVE1-: D13.2 (A), D15.1 (K), J9.2, Q1.3 (D)
/VALVE2-: D14.2 (A), D16.1 (K), J9.4, Q2.3 (D)
/VFD_COM: C21.2, J10.2, U7.3
/VFD_DI: C21.1, J10.1, U7.4
/VFD_EN: R35.1, R48.1, U5.11
/VLED1_A: D15.2 (A), R46.2
/VLED2_A: D16.2 (A), R47.2
/WD_CEXT: C17.1, U4.6 (Cext)
/WD_CLR: R29.2, U4.3 (~CLR)
/WD_OK: TP7.1 (1_1), U4.5 (Q), U5.1
/WD_RCEXT: C17.2, R30.2, U4.7 (RCext)
GND: C1.2, C2.2, C3.2, C4.2, C5.2, C16.2, C18.2, C19.2, C20.2, D2.2 (A), D11.1 (K), D12.1 (K), H1.1 (1_1), H2.1 (1_1), H3.1 (1_1), H4.1 (1_1), J1.2, J2.2, J2.8, J5.2, J11.3, Q1.2 (S), Q2.2 (S), R1.1, R32.2, R33.2, R34.2, R35.2, R44.2, R45.2, TP4.1 (1_1), U4.1 (~A), U4.4 (GND), U5.7 (GND), U6.1 (A0), U6.2 (A1), U6.3 (A2), U6.4 (A3), U6.5 (A4), U6.14 (VSS), U6.23 (~OE), U6.24 (A5), U6.25 (EXTCLK), U7.2

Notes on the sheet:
Low-side; SS34 flyback; start-assist ~290 mA, drain ~375 mA.
24 V in -> polyfuse -> series Schottky -> TVS = 24V_P; feeds Waveshare VIN, valves and 4-20 mA loops.
PWR_FLAGs (rail drive markers)
9. PWM (U6 PCA9685, 0x40)
SAFE = WD_OK * TEMP_OK; V1/V2_DRV = PWM_Vn * SAFE; VFD_EN = SAFE.
20 mA -> 2.0 V; <3.8 mA = open loop. AIN2 = 3V3_A/2 for ratiometric NTC maths, AIN3 = SAFE/2.
NTC 100k B~4000; shield to AGND at this end only. AIN0 rotor, AIN1 rotor 2, AIN2 motor, AIN3 TEMP_OK/2.
1. POWER INPUT & PROTECTION
11. VFD ENABLE
5. NTC ADC (U2, 0x49)
10. VALVE DRIVERS
7. WATCHDOG (U4 74LVC1G123)
4. PRESSURE ADC (U1, 0x48)
HEARTBEAT from PCA9685 LED4, 5 Hz while control loop runs; tw ~ 1 s; WD_OK low at power-up and when the heartbeat stops.
LED0 start-assist, LED1 drain, LED2/3 status LEDs, LED4 heartbeat; ~1.5 kHz, 50 % hold after pull-in.
Opto conducts only while SAFE is high. Wire to an SKI-70 DI set as NC external fault / coast stop.
12. MECHANICAL & TEST
6. HW OVER-TEMP CUTOUT (U3 LM393)
3. WAVESHARE HARNESS (H4) & I2C
2. 3V3 RAILS
8. SAFETY GATING (U5 74LVC08)
3V3_D comes from Waveshare H4 VCC (jumper H3 = 3V3). 3V3_A = 3V3_D via ferrite FB1. AGND ties to GND at R1 only, near the ADS.
H4 pin order: 1 VIN, 2 GND, 3 A, 4 B, 5 CANL NC, 6 CANH NC, 7 VCC, 8 GND, 9 SDA, 10 SCL. Waveshare already pulls up I2C with 4.7k; R2/R3 DNP. Set Waveshare SW1 RS485 termination ON. J11 = VFD Modbus pass-through, J5 = I2C debug header.
Ch A NTC1 rotor trips ~110 C (fw 105). Ch B NTC3 motor trips ~140 C (fw 130). 10M hysteresis ~3 K. Open-collector wired-AND -> TEMP_OK (high = OK).

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
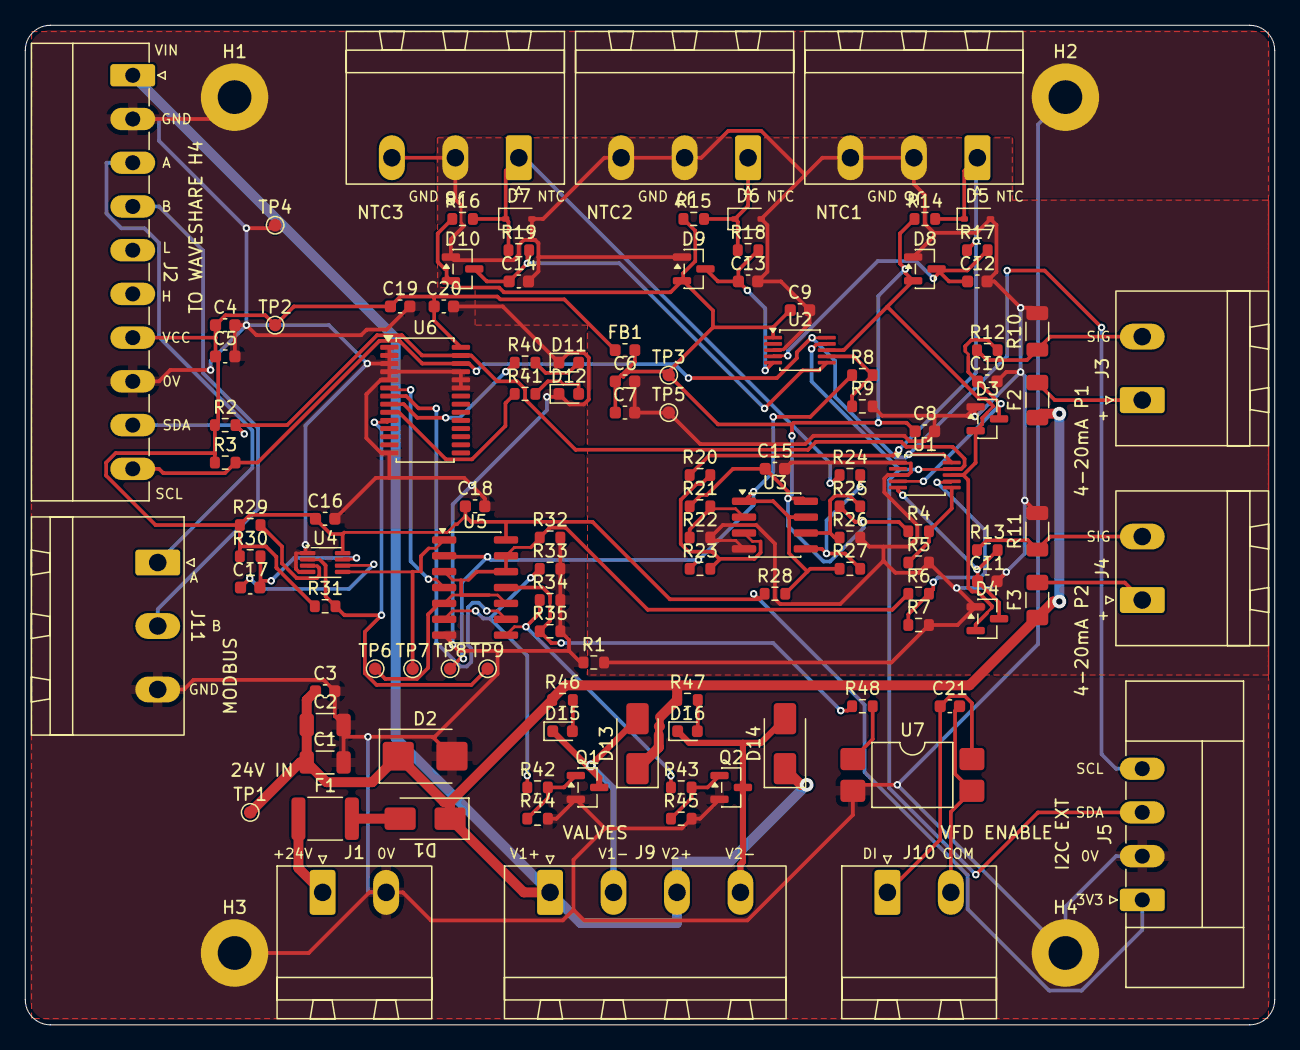
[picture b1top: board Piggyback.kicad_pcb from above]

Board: 2 copper layers, 100.0 x 80.0 mm, 118 parts (0 on the bottom side), 55 nets.

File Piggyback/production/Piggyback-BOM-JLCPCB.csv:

Comment,Designator,Footprint,LCSC Part #
10uF/50V,"C1,C2",C_1206_3216Metric,C13585
100nF/50V,"C3,C5,C7,C8,C9,C10,C11,C12,C13,C14,C15,C16,C18,C19,C21",C_0603_1608Metric,C14663
10uF/10V,"C4,C6,C20",C_0603_1608Metric,C19702
1uF/50V,C17,C_0603_1608Metric,C15849
SS54,D1,D_SMA,C22452
SMBJ30A,D2,D_SMB,C113998
BAV99,"D3,D4,D8,D9,D10",SOT-23,C2500
KT-0603R (red),"D11,D12,D15,D16",LED_0603_1608Metric,C2286
SS34,"D13,D14",D_SMA,C8678
1812L150/33GR,F1,Fuse_1812_4532Metric,C18198333
SMD1206P005TF,"F2,F3",Fuse_1206_3216Metric,C20797
600R@100MHz,FB1,L_0603_1608Metric,C1002
DMN6075S-7,"Q1,Q2",SOT-23,C155242
0R (R_TIE),R1,R_0603_1608Metric,C21189
10k,"R4,R5,R6,R7,R8,R9,R17,R18,R19,R28,R29,R31,R46,R47",R_0603_1608Metric,C25804
100R 1%,"R10,R11",R_1206_3216Metric,C17901
1k,"R12,R13,R40,R41",R_0603_1608Metric,C21190
33k 1%,"R14,R15,R16",R_0603_1608Metric,C4216
100k,"R20,R21,R24,R25,R32,R33,R34,R35,R44,R45",R_0603_1608Metric,C25803
15k 1%,R22,R_0603_1608Metric,C22809
10M,"R23,R27",R_0603_1608Metric,C7250
7.5k 1%,R26,R_0603_1608Metric,C23234
1M,R30,R_0603_1608Metric,C22935
100R,"R42,R43",R_0603_1608Metric,C22775
330R,R48,R_0603_1608Metric,C23138
ADS1115IDGSR,"U1,U2",TSSOP-10_3x3mm_P0.5mm,C37593
LM393DR2G,U3,SOIC-8_3.9x4.9mm_P1.27mm,C7955
74LVC1G123DC,U4,VSSOP-8_2.3x2mm_P0.5mm,C77273
SN74LVC08ADR,U5,SOIC-14_3.9x8.7mm_P1.27mm,C468253
PCA9685PW,U6,TSSOP-28_4.4x9.7mm_P0.65mm,C2678753
LTV-817S,U7,SMDIP-4_W9.53mm,C109227
